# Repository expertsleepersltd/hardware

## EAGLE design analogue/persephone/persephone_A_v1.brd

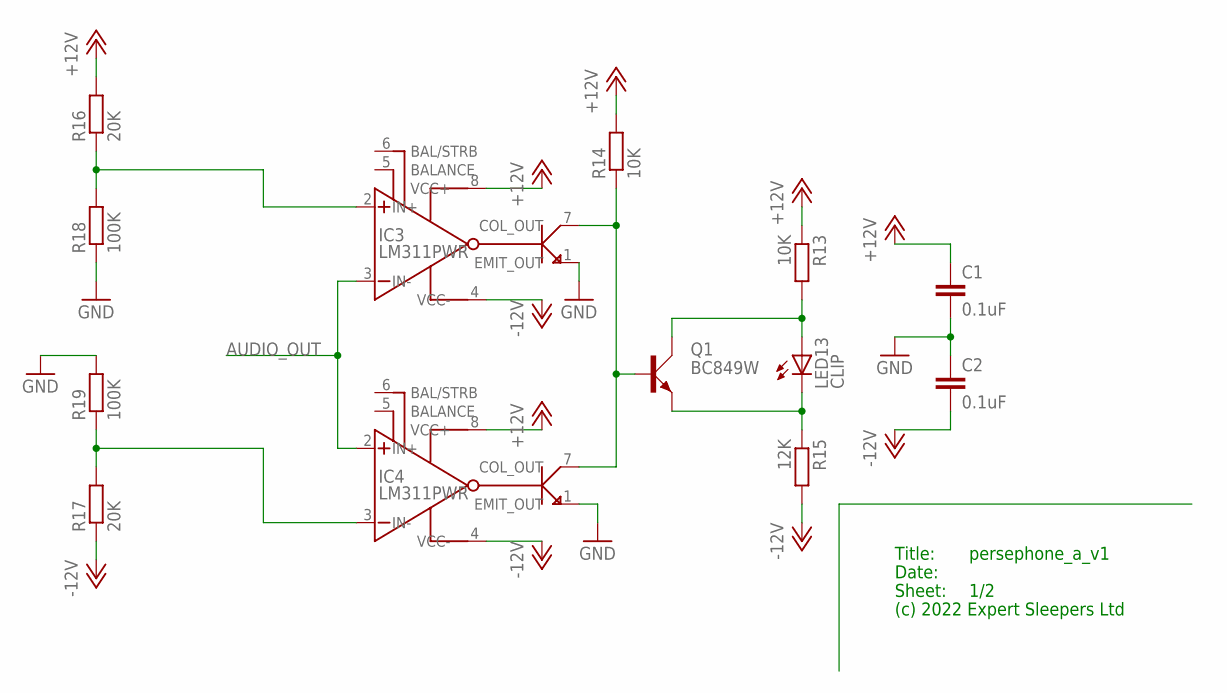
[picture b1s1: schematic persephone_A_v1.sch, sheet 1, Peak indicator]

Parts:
C1, C2: 0.1uF; C0402
IC3, IC4: LM311PWR; SOP65P640X120-8N
LED13: CLIP; L-710A8RS
Q1: BC849W; SOT323
R13, R14: 10K; R0603
R15: 12K; R0603
R16, R17: 20K; R0603
R18, R19: 100K; R0603

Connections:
+12V: C1.1, IC3.8 (VCC+), IC4.8 (VCC+), R13.1, R14.2, R16.2; also elsewhere on the board
-12V: C2.2, IC3.4 (VCC-), IC4.4 (VCC-), R15.2, R17.1; also elsewhere on the board
AUDIO_OUT: IC3.3 (IN-), IC4.2 (IN+); also elsewhere on the board
GND: C1.2, C2.1, IC3.1 (EMIT_OUT), IC4.1 (EMIT_OUT), R18.1, R19.2; also elsewhere on the board
unnamed: LED13.C, Q1.2 (E), R15.1
unnamed: LED13.A, Q1.3 (C), R13.2
unnamed: IC3.7 (COL_OUT), IC4.7 (COL_OUT), Q1.1 (B), R14.1
unnamed: IC3.2 (IN+), R16.1, R18.2
unnamed: IC4.3 (IN-), R17.2, R19.1

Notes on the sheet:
Title:
Date:
Sheet:
(c) 2022 Expert Sleepers Ltd

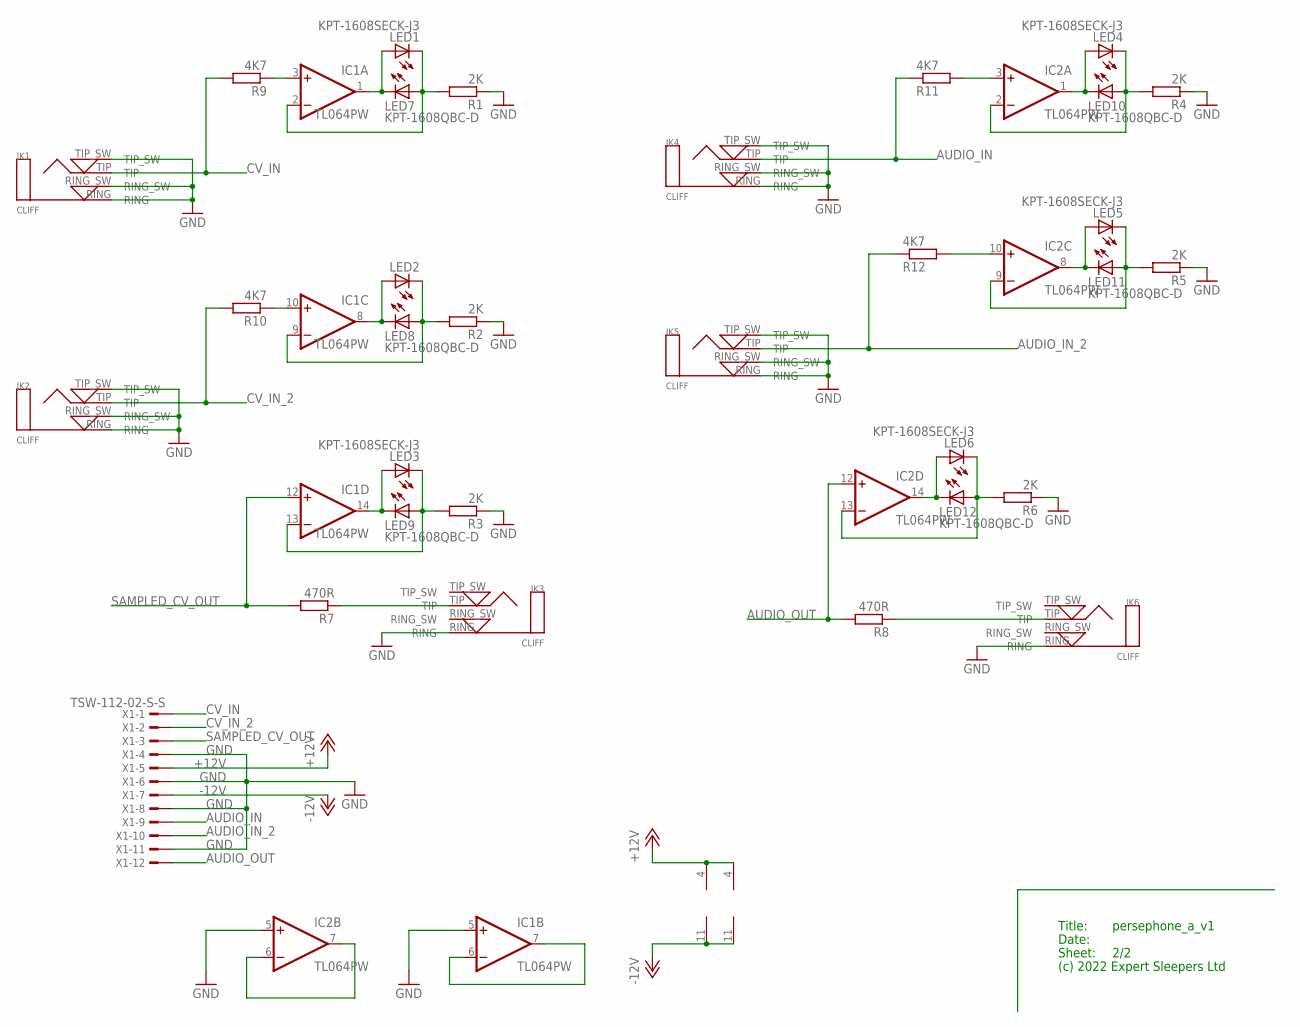
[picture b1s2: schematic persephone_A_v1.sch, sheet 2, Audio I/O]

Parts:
IC1, IC2: TL064PW; PW_R-PDSO-G14
JK1, JK2, JK3, JK4, JK5, JK6: CLIFF; CLIFF3.5MMPCB
LED1, LED2, LED3, LED4, LED5, LED6: KPT-1608SECK-J3; CHIPLED_0603_LEFT
LED7, LED8, LED9, LED10, LED11, LED12: KPT-1608QBC-D; CHIPLED_0603_RIGHT
R1, R2, R3, R4, R5, R6: 2K; R1206
R7, R8: 470R; R1206
R9, R10, R11, R12: 4K7; R1206
X1: TSW-112-02-S-S

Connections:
+12V: IC1.4 (V+), IC2.4 (V+), X1.5; also elsewhere on the board
-12V: IC1.11 (V-), IC2.11 (V-), X1.7; also elsewhere on the board
AUDIO_IN: JK4.TIP, R11.1, X1.9
AUDIO_IN_2: JK5.TIP, R12.1, X1.10
AUDIO_OUT: IC2.12 (+IN), R8.2, X1.12; also elsewhere on the board
CV_IN: JK1.TIP, R9.2, X1.1
CV_IN_2: JK2.TIP, R10.2, X1.2
GND: IC1.5 (+IN), IC2.5 (+IN), JK1.RING, JK1.RING_SW, JK1.TIP_SW, JK2.RING, JK2.RING_SW, JK2.TIP_SW, JK3.RING, JK4.RING, JK4.RING_SW, JK4.TIP_SW, JK5.RING, JK5.RING_SW, JK5.TIP_SW, JK6.RING, R1.1, R2.1, R3.1, R4.1, R5.1, R6.1, X1.4, X1.6, X1.8, X1.11; also elsewhere on the board
unnamed: IC2.6 (-IN), IC2.7 (OUT)
unnamed: IC1.14 (OUT), LED3.2 (A), LED9.2 (C)
unnamed: IC1.10 (+IN), R10.1
unnamed: IC1.13 (-IN), LED3.1 (C), LED9.1 (A), R3.2
unnamed: IC1.1 (OUT), LED1.2 (A), LED7.2 (C)
unnamed: IC2.10 (+IN), R12.2
unnamed: IC1.2 (-IN), LED1.1 (C), LED7.1 (A), R1.2
unnamed: IC1.3 (+IN), R9.1
unnamed: IC1.8 (OUT), LED2.2 (A), LED8.2 (C)
unnamed: IC1.9 (-IN), LED2.1 (C), LED8.1 (A), R2.2
unnamed: IC1.6 (-IN), IC1.7 (OUT)
unnamed: JK3.TIP, R7.1
unnamed: IC2.3 (+IN), R11.2
unnamed: IC2.8 (OUT), LED5.2 (A), LED11.2 (C)
unnamed: IC2.9 (-IN), LED5.1 (C), LED11.1 (A), R5.2
unnamed: IC2.14 (OUT), LED6.2 (A), LED12.2 (C)
unnamed: IC2.13 (-IN), LED6.1 (C), LED12.1 (A), R6.2
unnamed: IC2.1 (OUT), LED4.2 (A), LED10.2 (C)
unnamed: IC2.2 (-IN), LED4.1 (C), LED10.1 (A), R4.2
unnamed: JK6.TIP, R8.1
SAMPLED_CV_OUT: IC1.12 (+IN), R7.2, X1.3

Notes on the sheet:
Title:
Date:
Sheet:
(c) 2022 Expert Sleepers Ltd

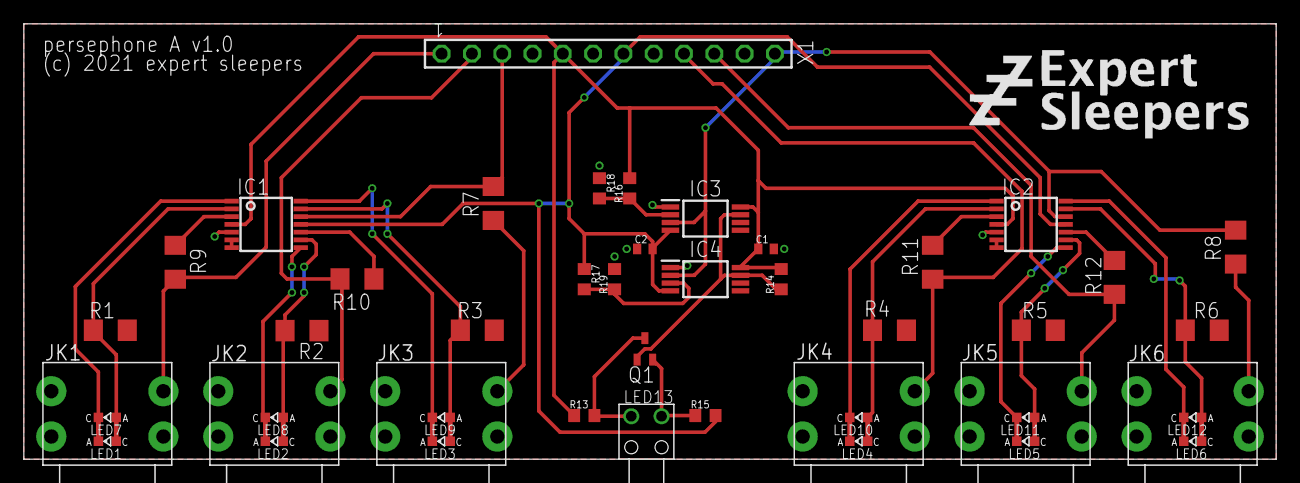
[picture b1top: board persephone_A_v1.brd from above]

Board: 2 copper layers, 105.0 x 36.5 mm, 47 parts (0 on the bottom side), 34 nets.

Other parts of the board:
U$1: ES_ZZZ_TEXT_TPLACE_1IN_600DPI

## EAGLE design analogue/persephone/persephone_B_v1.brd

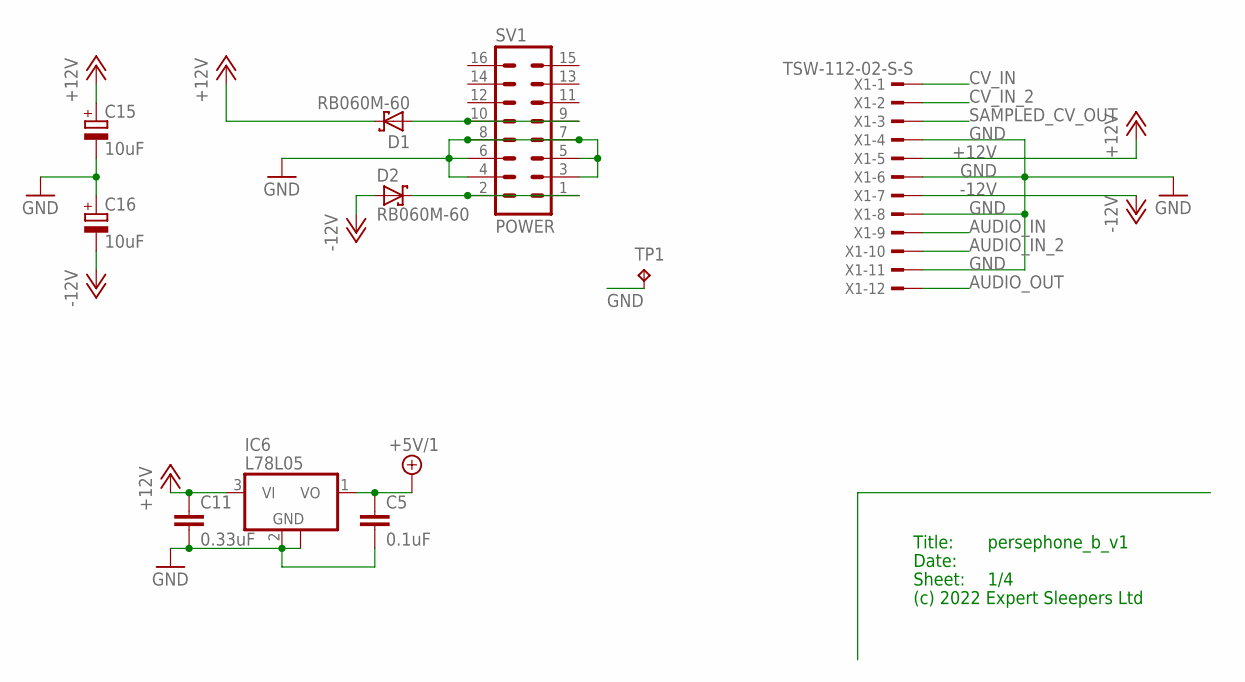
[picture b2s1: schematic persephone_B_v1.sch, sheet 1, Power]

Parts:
C5: 0.1uF; C0402
C11: 0.33uF; C0805
C15, C16: 10uF; UD-4X5,8_NICHICON
D1, D2: RB060M-60; SOD123FL
IC6: L78L05; SOT89
SV1: POWER; ML16
TP1: RA2; P1-13
X1: TSW-112-02-S-S

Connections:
+5V/1: C5.1, IC6.1 (VO); also elsewhere on the board
+12V: C11.1, C15.+, D1.C, IC6.3 (VI), X1.5; also elsewhere on the board
-12V: C16.-, D2.A, X1.7; also elsewhere on the board
AUDIO_IN: X1.9; also elsewhere on the board
AUDIO_IN_2: X1.10; also elsewhere on the board
AUDIO_OUT: X1.12; also elsewhere on the board
CV_IN: X1.1; also elsewhere on the board
CV_IN_2: X1.2; also elsewhere on the board
GND: C5.2, C11.2, C15.-, C16.+, IC6.2 (GND), IC6.2@1 (GND), SV1.3, SV1.4, SV1.5, SV1.6, SV1.7, SV1.8, TP1.TP, X1.4, X1.6, X1.8, X1.11; also elsewhere on the board
unnamed: D2.C, SV1.1, SV1.2
unnamed: D1.A, SV1.9, SV1.10
SAMPLED_CV_OUT: X1.3; also elsewhere on the board

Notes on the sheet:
Title:
Date:
Sheet:
(c) 2022 Expert Sleepers Ltd

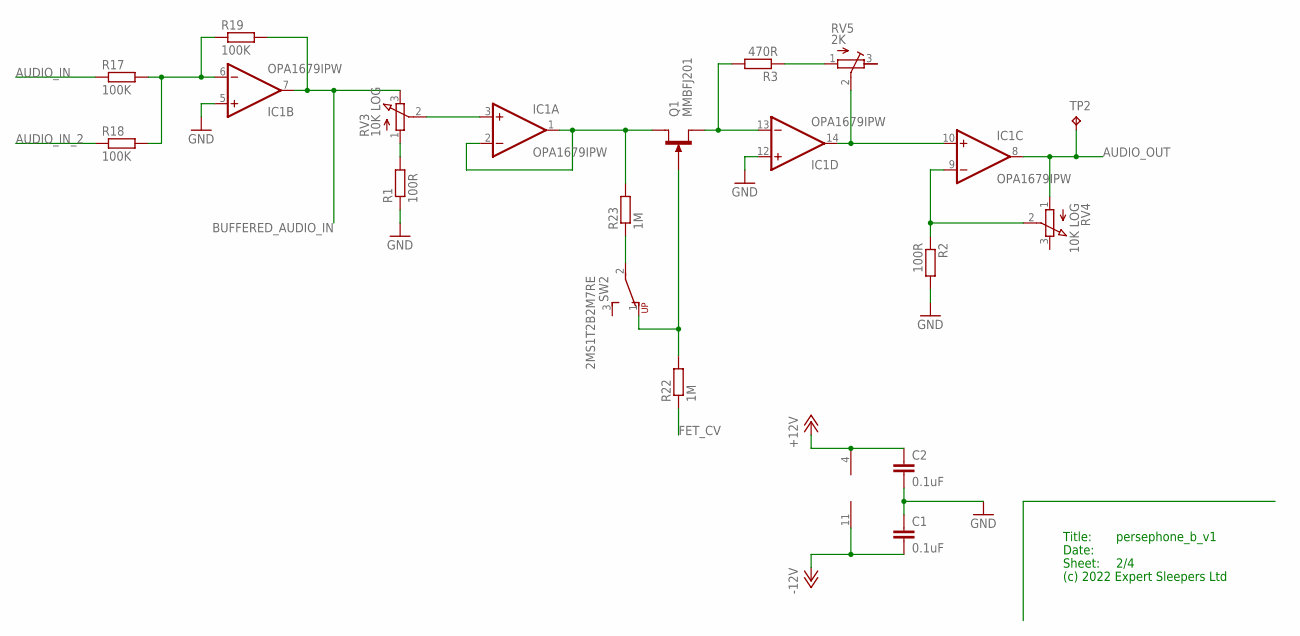
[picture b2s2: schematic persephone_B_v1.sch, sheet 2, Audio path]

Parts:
C1, C2: 0.1uF; C0402
IC1: OPA1679IPW; PW_R-PDSO-G14
Q1: MMBFJ201; SOT23
R1, R2: 100R; R0603
R3: 470R; R0603
R17, R18, R19: 100K; R0603
R22, R23: 1M; R0603
RV3, RV4: 10K LOG; RD1610NOA0X
RV5: 2K; TC33X
SW2: 2MS1T2B2M7RE
TP2: RA2; P1-13

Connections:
+12V: C2.1, IC1.4 (V+); also elsewhere on the board
-12V: C1.2, IC1.11 (V-); also elsewhere on the board
ATTEN_IN: IC1.3 (+IN), RV3.2 (S)
AUDIO_IN: R17.1; also elsewhere on the board
AUDIO_IN_2: R18.1; also elsewhere on the board
AUDIO_OUT: IC1.8 (OUT), RV4.1 (A), TP2.TP; also elsewhere on the board
BUFFERED_AUDIO_IN: IC1.7 (OUT), R19.2, RV3.3 (E); also elsewhere on the board
FET_CV: R22.1; also elsewhere on the board
GND: C1.1, C2.2, IC1.5 (+IN), IC1.12 (+IN), R1.1, R2.2; also elsewhere on the board
unnamed: IC1.9 (-IN), R2.1, RV4.2 (S)
unnamed: IC1.10 (+IN), IC1.14 (OUT), RV5.2 (S)
unnamed: IC1.1 (OUT), IC1.2 (-IN), Q1.1 (D), R23.2
unnamed: R1.2, RV3.1 (A)
unnamed: Q1.3 (G), R22.2, SW2.1 (RU)
unnamed: R3.1, RV5.1 (A)
unnamed: IC1.13 (-IN), Q1.2 (S), R3.2
unnamed: R23.1, SW2.2 (PR)
unnamed: IC1.6 (-IN), R17.2, R18.2, R19.1

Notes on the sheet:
Title:
Date:
Sheet:
(c) 2022 Expert Sleepers Ltd

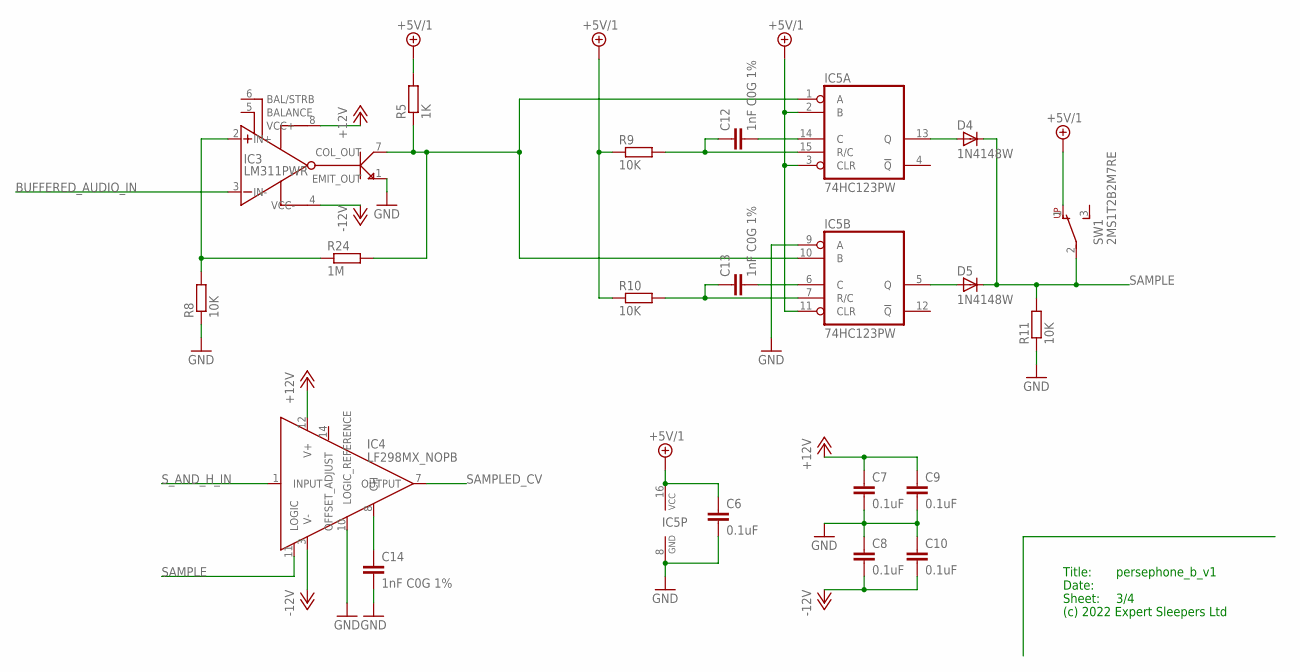
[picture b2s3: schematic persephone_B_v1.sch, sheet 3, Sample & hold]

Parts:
C6, C7, C8, C9, C10: 0.1uF; C0402
C12, C13, C14: 1nF C0G 1%; C0603
D4, D5: 1N4148W; SOD123
IC3: LM311PWR; SOP65P640X120-8N
IC4: LF298MX_NOPB; SOIC127P600X175-14N
IC5: 74HC123PW; PW_R-PDSO-G16
R5: 1K; R0603
R8, R9, R10, R11: 10K; R0603
R24: 1M; R0603
SW1: 2MS1T2B2M7RE

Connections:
+5V/1: C6.1, IC5.2 (B), IC5.3 (CLR), IC5.11 (CLR), IC5.16 (VCC), R5.2, R9.1, R10.1, SW1.1 (RU); also elsewhere on the board
+12V: C7.1, C9.1, IC3.8 (VCC+), IC4.12 (V+); also elsewhere on the board
-12V: C8.2, C10.2, IC3.4 (VCC-), IC4.3 (V-); also elsewhere on the board
BUFFERED_AUDIO_IN: IC3.3 (IN-); also elsewhere on the board
COMP_OUT: IC3.7 (COL_OUT), IC5.1 (A), IC5.10 (B), R5.1, R24.2
GND: C6.2, C7.2, C8.1, C9.2, C10.1, C14.2, IC3.1 (EMIT_OUT), IC4.10 (LOGIC_REFERENCE), IC5.8 (GND), IC5.9 (A), R8.1, R11.1; also elsewhere on the board
unnamed: IC3.2 (IN+), R8.2, R24.1
unnamed: C13.1, IC5.7 (R/C), R10.2
unnamed: C12.1, IC5.15 (R/C), R9.2
unnamed: D4.2 (A), IC5.13 (Q)
unnamed: D5.2 (A), IC5.5 (Q)
unnamed: C12.2, IC5.14 (C)
unnamed: C13.2, IC5.6 (C)
unnamed: C14.1, IC4.8 (CH)
SAMPLE: D4.1 (C), D5.1 (C), IC4.11 (LOGIC), R11.2, SW1.2 (PR)
SAMPLED_CV: IC4.7 (OUTPUT); also elsewhere on the board
S_AND_H_IN: IC4.1 (INPUT); also elsewhere on the board

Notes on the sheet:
Title:
Date:
Sheet:
(c) 2022 Expert Sleepers Ltd

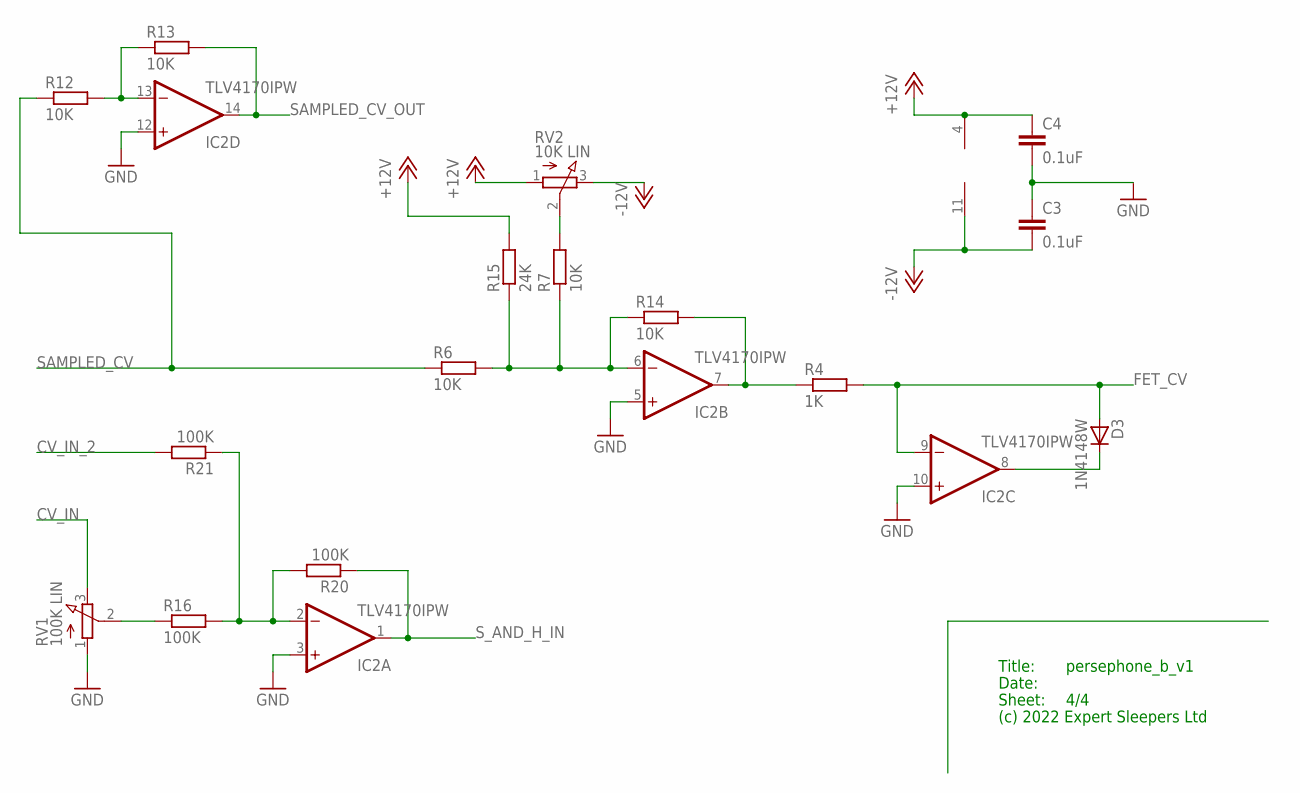
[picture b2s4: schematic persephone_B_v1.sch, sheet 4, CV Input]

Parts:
C3, C4: 0.1uF; C0402
D3: 1N4148W; SOD123
IC2: TLV4170IPW; PW_R-PDSO-G14
R4: 1K; R0603
R6, R7, R12, R13, R14: 10K; R0603
R15: 24K; R0603
R16, R20, R21: 100K; R0603
RV1: 100K LIN; RD1610NOA0X
RV2: 10K LIN; RD1610NOA0X

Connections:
+12V: C4.1, IC2.4 (V+), R15.2, RV2.1 (A); also elsewhere on the board
-12V: C3.2, IC2.11 (V-), RV2.3 (E); also elsewhere on the board
CV_IN: RV1.3 (E); also elsewhere on the board
CV_IN_2: R21.2; also elsewhere on the board
FET_CV: D3.2 (A), IC2.9 (-IN), R4.2; also elsewhere on the board
GND: C3.1, C4.2, IC2.3 (+IN), IC2.5 (+IN), IC2.10 (+IN), IC2.12 (+IN), RV1.1 (A); also elsewhere on the board
unnamed: IC2.2 (-IN), R16.2, R20.2, R21.1
unnamed: R16.1, RV1.2 (S)
unnamed: IC2.6 (-IN), R6.2, R7.1, R14.1, R15.1
unnamed: IC2.13 (-IN), R12.2, R13.1
unnamed: IC2.7 (OUT), R4.1, R14.2
unnamed: R7.2, RV2.2 (S)
unnamed: D3.1 (C), IC2.8 (OUT)
SAMPLED_CV: R6.1, R12.1; also elsewhere on the board
SAMPLED_CV_OUT: IC2.14 (OUT), R13.2; also elsewhere on the board
S_AND_H_IN: IC2.1 (OUT), R20.1; also elsewhere on the board

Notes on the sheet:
Title:
Date:
Sheet:
(c) 2022 Expert Sleepers Ltd

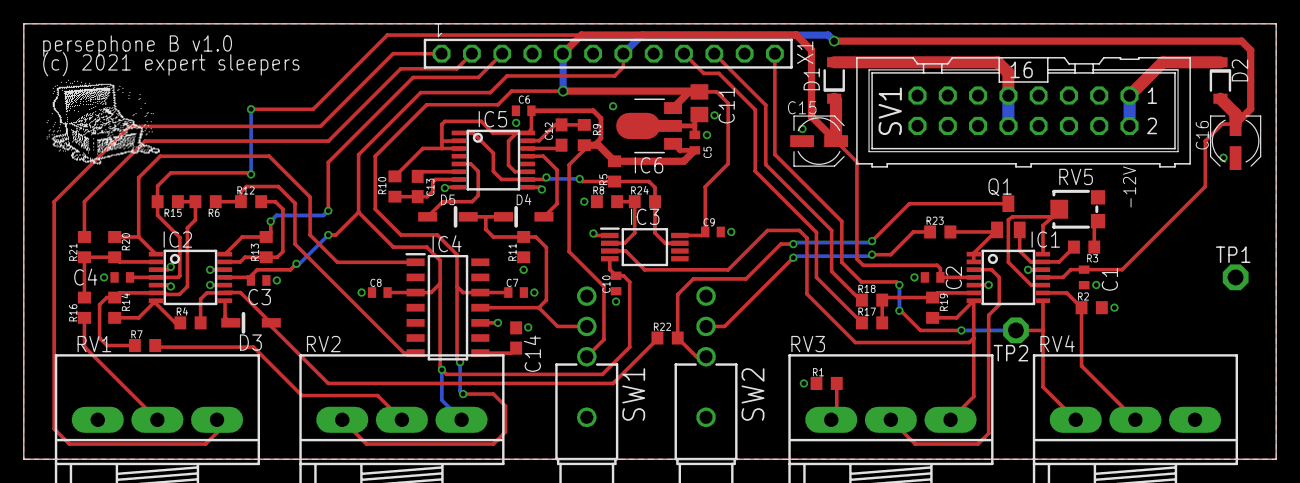
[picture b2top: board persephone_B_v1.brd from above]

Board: 2 copper layers, 105.0 x 36.5 mm, 64 parts (0 on the bottom side), 43 nets.

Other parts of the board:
U$2: TREASURE_10MM_300DPI

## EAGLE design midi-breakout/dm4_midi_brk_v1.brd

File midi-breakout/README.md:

MIDI Breakout
=====

https://expert-sleepers.co.uk/dm4midibreakout.html

Copyright (c) 2017 Expert Sleepers Ltd

Please refer to [LICENSE.md](LICENSE.md) for licensing information.

Please note that Expert Sleepers® is a registered trade mark in the UK. Remove any branding before making a derivative work.

Front panel layout is [here](../panels).

Board and schematic are in [EAGLE](https://en.wikipedia.org/wiki/EAGLE_(program)) format.

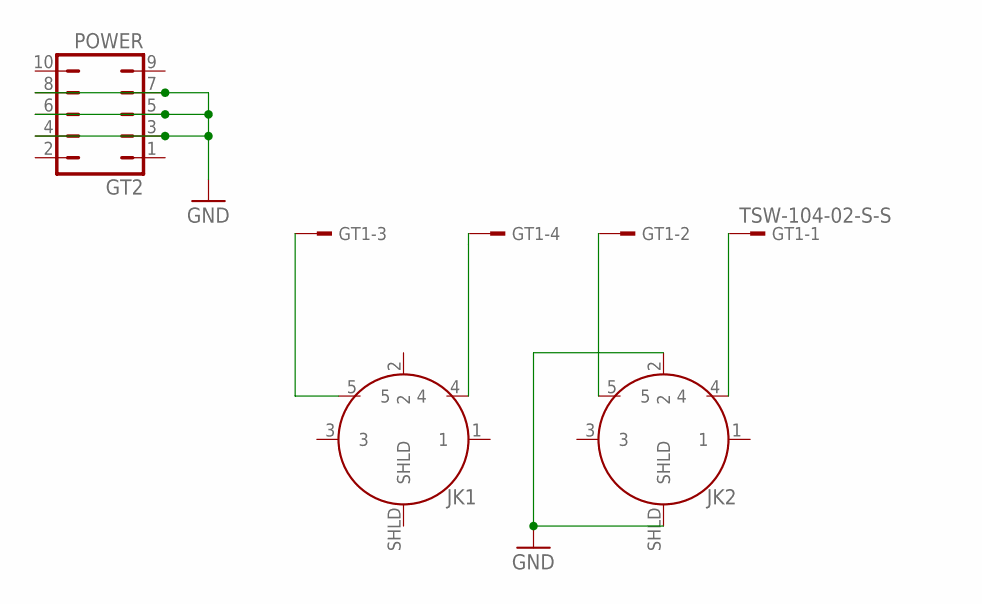
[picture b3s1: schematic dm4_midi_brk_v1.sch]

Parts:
GT1: TSW-104-02-S-S
GT2: POWER; JP5Q
JK1, JK2: 13HP021PCB

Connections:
GND: GT2.3, GT2.4, GT2.5, GT2.6, GT2.7, GT2.8, JK2.2, JK2.SHLD
unnamed: GT1.3, JK1.5
unnamed: GT1.1, JK2.4
unnamed: GT1.2, JK2.5
unnamed: GT1.4, JK1.4

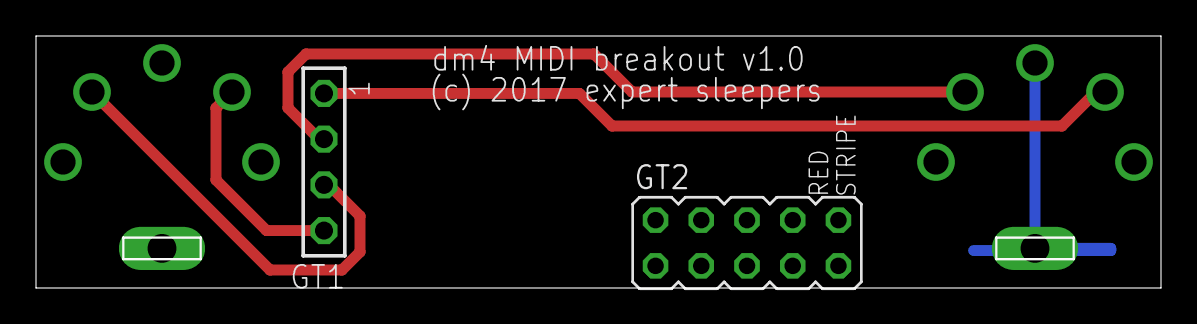
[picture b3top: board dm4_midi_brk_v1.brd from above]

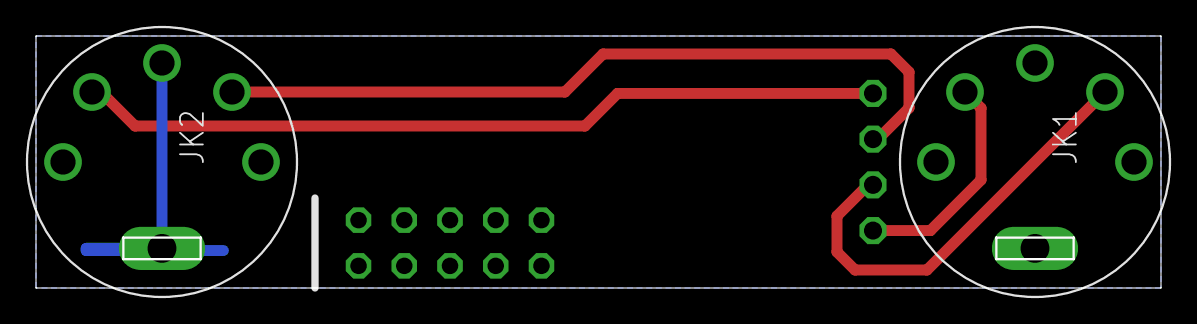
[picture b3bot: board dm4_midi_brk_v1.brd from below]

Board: 2 copper layers, 62.5 x 14.0 mm, 4 parts (2 on the bottom side), 5 nets.

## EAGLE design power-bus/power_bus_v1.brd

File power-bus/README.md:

Power Bus
=====

A Eurorack format power backplane.

Copyright (c) 2021 Expert Sleepers Ltd

Please refer to [LICENSE.md](LICENSE.md) for licensing information.

Please note that Expert Sleepers® is a registered trade mark in the UK. Remove any branding before making a derivative work.

Board and schematic are in [EAGLE](https://en.wikipedia.org/wiki/EAGLE_(program)) format.

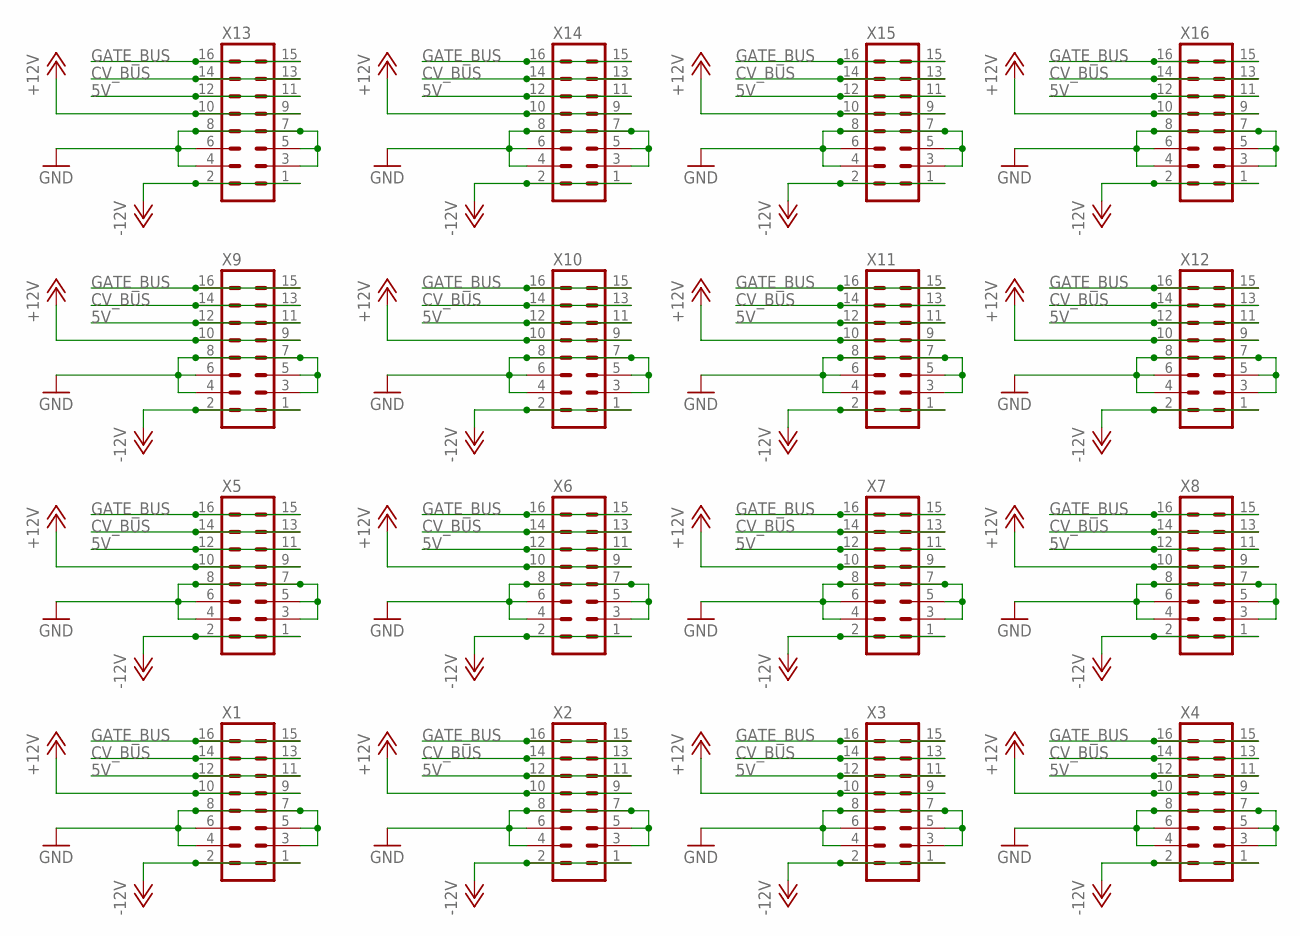
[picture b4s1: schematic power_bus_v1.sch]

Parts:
X1, X2, X3, X4, X5, X6, X7, X8, X9, X10, X11, X12, X13, X14, X15, X16: ML16

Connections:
5V: X1.11, X1.12, X2.11, X2.12, X3.11, X3.12, X4.11, X4.12, X5.11, X5.12, X6.11, X6.12, X7.11, X7.12, X8.11, X8.12, X9.11, X9.12, X10.11, X10.12, X11.11, X11.12, X12.11, X12.12, X13.11, X13.12, X14.11, X14.12, X15.11, X15.12, X16.11, X16.12
+12V: X1.9, X1.10, X2.9, X2.10, X3.9, X3.10, X4.9, X4.10, X5.9, X5.10, X6.9, X6.10, X7.9, X7.10, X8.9, X8.10, X9.9, X9.10, X10.9, X10.10, X11.9, X11.10, X12.9, X12.10, X13.9, X13.10, X14.9, X14.10, X15.9, X15.10, X16.9, X16.10
-12V: X1.1, X1.2, X2.1, X2.2, X3.1, X3.2, X4.1, X4.2, X5.1, X5.2, X6.1, X6.2, X7.1, X7.2, X8.1, X8.2, X9.1, X9.2, X10.1, X10.2, X11.1, X11.2, X12.1, X12.2, X13.1, X13.2, X14.1, X14.2, X15.1, X15.2, X16.1, X16.2
CV_BUS: X1.13, X1.14, X2.13, X2.14, X3.13, X3.14, X4.13, X4.14, X5.13, X5.14, X6.13, X6.14, X7.13, X7.14, X8.13, X8.14, X9.13, X9.14, X10.13, X10.14, X11.13, X11.14, X12.13, X12.14, X13.13, X13.14, X14.13, X14.14, X15.13, X15.14, X16.13, X16.14
GATE_BUS: X1.15, X1.16, X2.15, X2.16, X3.15, X3.16, X4.15, X4.16, X5.15, X5.16, X6.15, X6.16, X7.15, X7.16, X8.15, X8.16, X9.15, X9.16, X10.15, X10.16, X11.15, X11.16, X12.15, X12.16, X13.15, X13.16, X14.15, X14.16, X15.15, X15.16, X16.15, X16.16
GND: X1.3, X1.4, X1.5, X1.6, X1.7, X1.8, X2.3, X2.4, X2.5, X2.6, X2.7, X2.8, X3.3, X3.4, X3.5, X3.6, X3.7, X3.8, X4.3, X4.4, X4.5, X4.6, X4.7, X4.8, X5.3, X5.4, X5.5, X5.6, X5.7, X5.8, X6.3, X6.4, X6.5, X6.6, X6.7, X6.8, X7.3, X7.4, X7.5, X7.6, X7.7, X7.8, X8.3, X8.4, X8.5, X8.6, X8.7, X8.8, X9.3, X9.4, X9.5, X9.6, X9.7, X9.8, X10.3, X10.4, X10.5, X10.6, X10.7, X10.8, X11.3, X11.4, X11.5, X11.6, X11.7, X11.8, X12.3, X12.4, X12.5, X12.6, X12.7, X12.8, X13.3, X13.4, X13.5, X13.6, X13.7, X13.8, X14.3, X14.4, X14.5, X14.6, X14.7, X14.8, X15.3, X15.4, X15.5, X15.6, X15.7, X15.8, X16.3, X16.4, X16.5, X16.6, X16.7, X16.8

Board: 2 copper layers, 16 parts (0 on the bottom side), 6 nets, no tracks yet.

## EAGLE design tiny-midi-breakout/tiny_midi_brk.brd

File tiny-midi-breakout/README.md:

Tiny MIDI Breakout
=====

https://expert-sleepers.co.uk/tinymidibreakout.html

Copyright (c) 2021 Expert Sleepers Ltd

Please refer to [LICENSE.md](LICENSE.md) for licensing information.

Please note that Expert Sleepers® is a registered trade mark in the UK. Remove any branding before making a derivative work.

Front panel layout is [here](../panels).

Board and schematic are in [EAGLE](https://en.wikipedia.org/wiki/EAGLE_(program)) format.

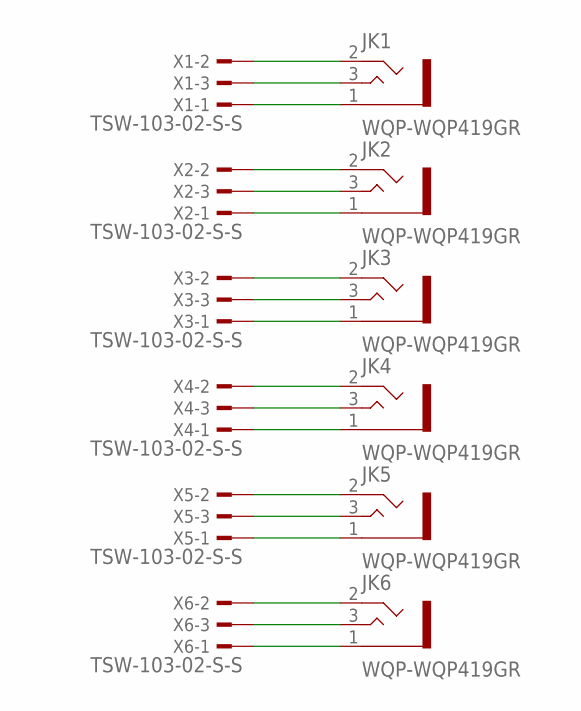
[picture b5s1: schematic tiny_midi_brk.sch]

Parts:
JK1, JK2, JK3, JK4, JK5, JK6: WQP-WQP419GR; WQP-PJ301M-12_JACK_TRS
X1, X2, X3, X4, X5, X6: TSW-103-02-S-S

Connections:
unnamed: JK1.1, X1.1
unnamed: JK1.2, X1.2
unnamed: JK1.3, X1.3
unnamed: JK2.1, X2.1
unnamed: JK2.2, X2.2
unnamed: JK2.3, X2.3
unnamed: JK3.1, X3.1
unnamed: JK3.2, X3.2
unnamed: JK3.3, X3.3
unnamed: JK4.1, X4.1
unnamed: JK4.2, X4.2
unnamed: JK4.3, X4.3
unnamed: JK5.1, X5.1
unnamed: JK5.2, X5.2
unnamed: JK5.3, X5.3
unnamed: JK6.1, X6.1
unnamed: JK6.2, X6.2
unnamed: JK6.3, X6.3

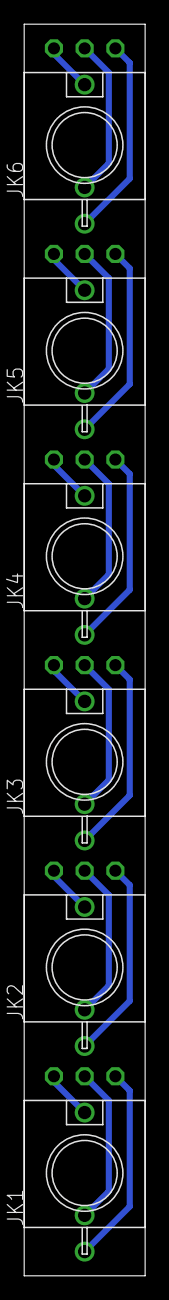
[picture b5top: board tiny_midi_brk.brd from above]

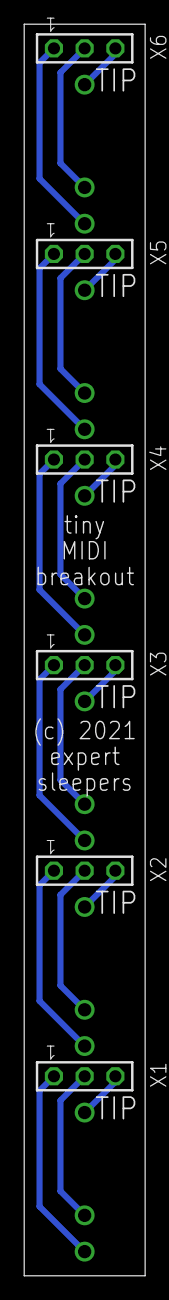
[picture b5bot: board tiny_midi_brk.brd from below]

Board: 2 copper layers, 10.0 x 103.5 mm, 12 parts (6 on the bottom side), 18 nets.
